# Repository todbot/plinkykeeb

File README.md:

# plinkykeeb

Simple MIDI controller using KB2040 and computer key switches, in Cherry MX or Kailh Choc versions

Also see: https://twitter.com/todbot/status/1492324272714366980__

And this demo video:

https://user-images.githubusercontent.com/274093/153778157-13a1d3d5-e82a-40dc-8635-7ddb3dfab898.mp4

Comparison in heights:

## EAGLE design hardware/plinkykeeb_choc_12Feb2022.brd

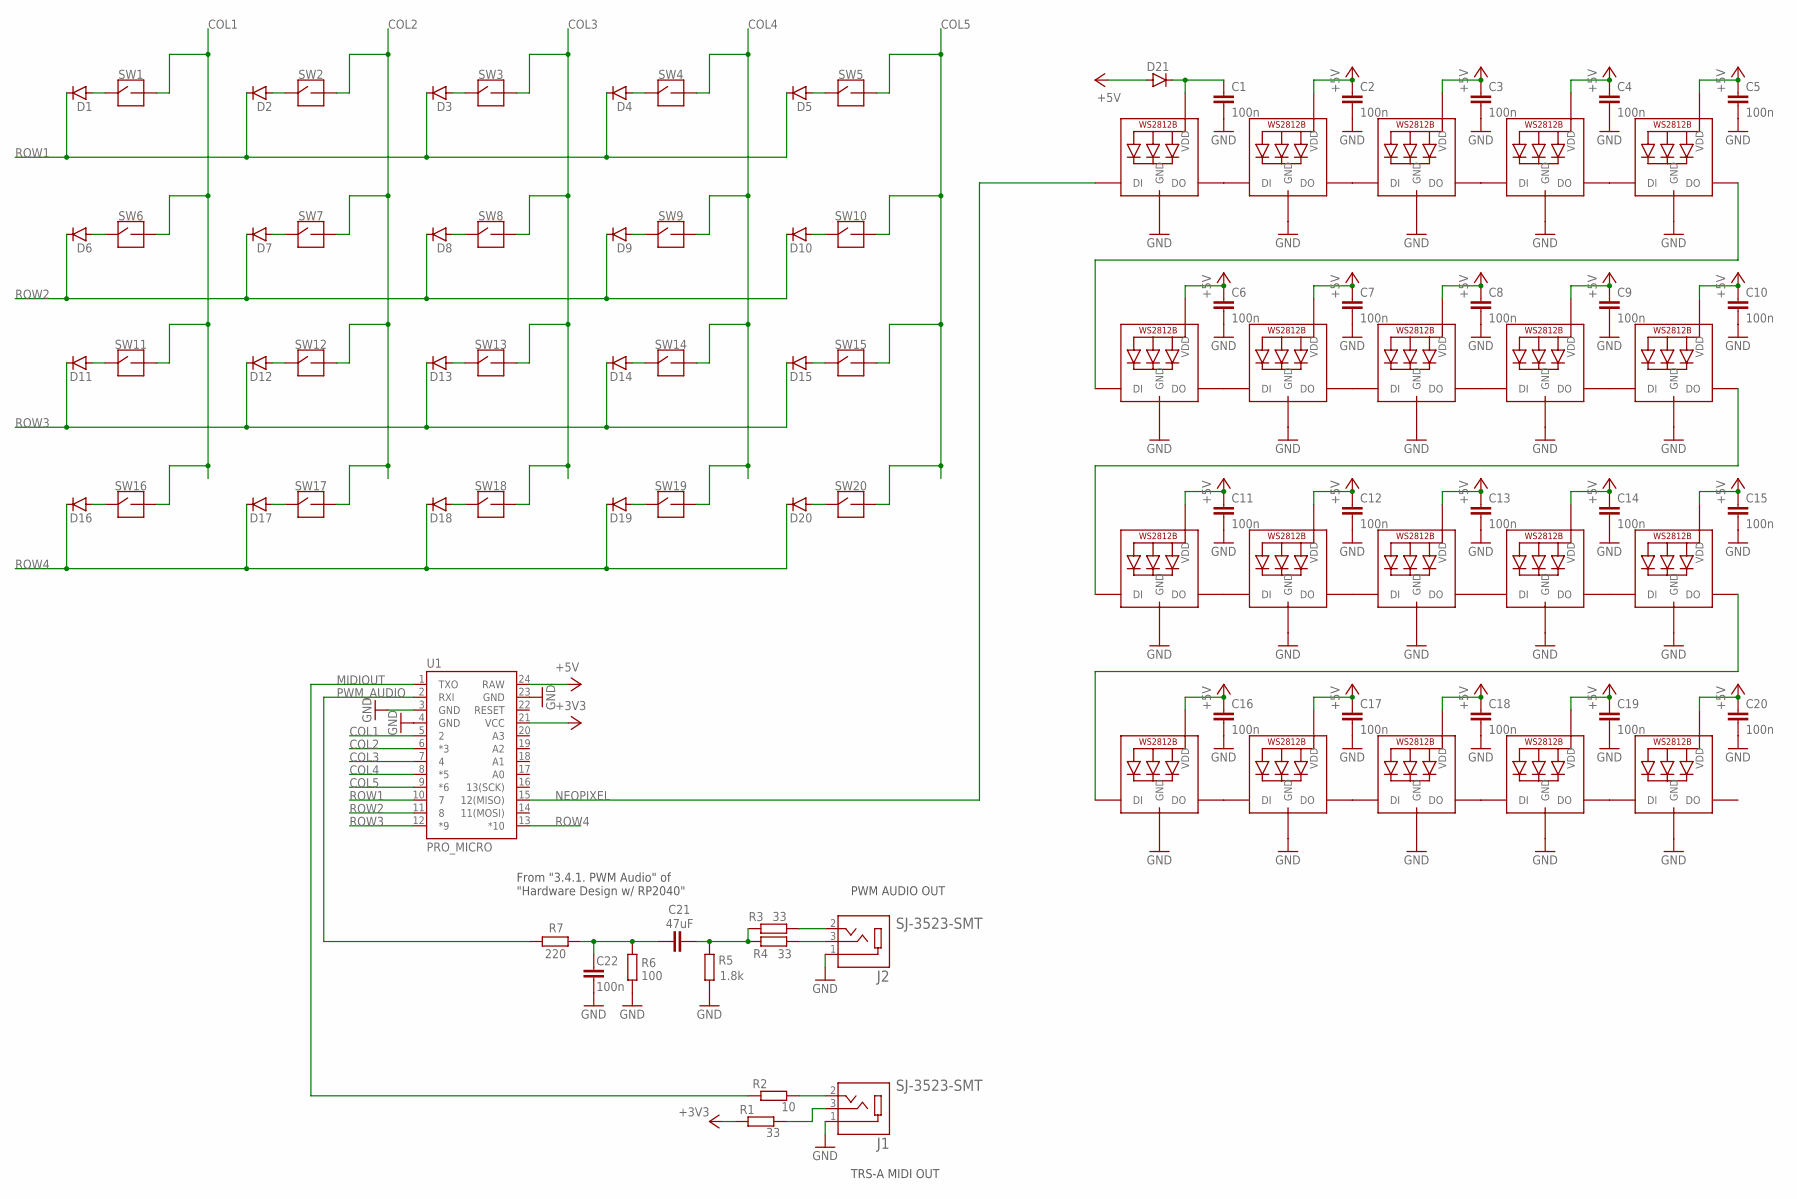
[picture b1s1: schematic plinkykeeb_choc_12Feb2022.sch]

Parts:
C1, C2, C3, C4, C5, C6, C7, C8, C9, C10, C11, C12, C13, C14, C15, C16, C17, C18, C19, C20, C22: 100n; C0805
C21: 47uF; C0805
D1, D2, D3, D4, D5, D6, D7, D8, D9, D10, D11, D12, D13, D14, D15, D16, D17, D18, D19, D20, D21: D-SOD123; SOD123
J1, J2: SJ-3523-SMT; CUI_SJ-3523-SMT
LED1, LED2, LED3, LED4, LED5, LED6, LED7, LED8, LED9, LED10, LED11, LED12, LED13, LED14, LED15, LED16, LED17, LED18, LED19, LED20: MICROBUILDER_WS2812B_SK6812E; MICROBUILDER_NEO3535_REVERSE
R1, R3, R4: 33; R0805
R2: 10; R0805
R5: 1.8k; R0805
R6: 100; R0805
R7: 220; R0805
SW1, SW2, SW3, SW4, SW5, SW6, SW7, SW8, SW9, SW10, SW11, SW12, SW13, SW14, SW15, SW16, SW17, SW18, SW19, SW20: KBD_SWITCHKALIH_CHOC_SOCKET; KALIH_SOCKET_CHOC
U1: PRO_MICRO; SPARKFUN_PRO_MICRO

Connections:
+3V3: R1.2, U1.21 (VCC)
+5V: C2.1, C3.1, C4.1, C5.1, C6.1, C7.1, C8.1, C9.1, C10.1, C11.1, C12.1, C13.1, C14.1, C15.1, C16.1, C17.1, C18.1, C19.1, C20.1, D21.2 (A), LED2.1-VDD (VDD), LED3.1-VDD (VDD), LED4.1-VDD (VDD), LED5.1-VDD (VDD), LED6.1-VDD (VDD), LED7.1-VDD (VDD), LED8.1-VDD (VDD), LED9.1-VDD (VDD), LED10.1-VDD (VDD), LED11.1-VDD (VDD), LED12.1-VDD (VDD), LED13.1-VDD (VDD), LED14.1-VDD (VDD), LED15.1-VDD (VDD), LED16.1-VDD (VDD), LED17.1-VDD (VDD), LED18.1-VDD (VDD), LED19.1-VDD (VDD), LED20.1-VDD (VDD), U1.24 (RAW)
COL1: SW1.2, SW6.2, SW11.2, SW16.2, U1.5 (2)
COL2: SW2.2, SW7.2, SW12.2, SW17.2, U1.6 (*3)
COL3: SW3.2, SW8.2, SW13.2, SW18.2, U1.7 (4)
COL4: SW4.2, SW9.2, SW14.2, SW19.2, U1.8 (*5)
COL5: SW5.2, SW10.2, SW15.2, SW20.2, U1.9 (*6)
GND: C1.2, C2.2, C3.2, C4.2, C5.2, C6.2, C7.2, C8.2, C9.2, C10.2, C11.2, C12.2, C13.2, C14.2, C15.2, C16.2, C17.2, C18.2, C19.2, C20.2, C22.2, J1.1, J2.1, LED1.3-GND (GND), LED2.3-GND (GND), LED3.3-GND (GND), LED4.3-GND (GND), LED5.3-GND (GND), LED6.3-GND (GND), LED7.3-GND (GND), LED8.3-GND (GND), LED9.3-GND (GND), LED10.3-GND (GND), LED11.3-GND (GND), LED12.3-GND (GND), LED13.3-GND (GND), LED14.3-GND (GND), LED15.3-GND (GND), LED16.3-GND (GND), LED17.3-GND (GND), LED18.3-GND (GND), LED19.3-GND (GND), LED20.3-GND (GND), R5.2, R6.1, U1.3 (GND), U1.4 (GND), U1.23 (GND)
MIDIOUT: R2.2, U1.1 (TXO)
unnamed: LED1.2-DOUT (DO), LED2.4-DIN (DI)
unnamed: LED2.2-DOUT (DO), LED3.4-DIN (DI)
unnamed: LED3.2-DOUT (DO), LED4.4-DIN (DI)
unnamed: LED4.2-DOUT (DO), LED5.4-DIN (DI)
unnamed: LED5.2-DOUT (DO), LED6.4-DIN (DI)
unnamed: D1.2 (A), SW1.1
unnamed: D2.2 (A), SW2.1
unnamed: D3.2 (A), SW3.1
unnamed: D4.2 (A), SW4.1
unnamed: D5.2 (A), SW5.1
unnamed: C1.1, D21.1 (C), LED1.1-VDD (VDD)
unnamed: D6.2 (A), SW6.1
unnamed: D18.2 (A), SW18.1
unnamed: D8.2 (A), SW8.1
unnamed: D9.2 (A), SW9.1
unnamed: D10.2 (A), SW10.1
unnamed: D11.2 (A), SW11.1
unnamed: D12.2 (A), SW12.1
unnamed: D13.2 (A), SW13.1
unnamed: D14.2 (A), SW14.1
unnamed: D15.2 (A), SW15.1
unnamed: D16.2 (A), SW16.1
unnamed: D17.2 (A), SW17.1
unnamed: D19.2 (A), SW19.1
unnamed: D20.2 (A), SW20.1
unnamed: LED7.2-DOUT (DO), LED8.4-DIN (DI)
unnamed: LED8.2-DOUT (DO), LED9.4-DIN (DI)
unnamed: LED9.2-DOUT (DO), LED10.4-DIN (DI)
unnamed: LED10.2-DOUT (DO), LED11.4-DIN (DI)
unnamed: LED11.2-DOUT (DO), LED12.4-DIN (DI)
unnamed: LED6.2-DOUT (DO), LED7.4-DIN (DI)
unnamed: D7.2 (A), SW7.1
unnamed: LED13.2-DOUT (DO), LED14.4-DIN (DI)
unnamed: LED14.2-DOUT (DO), LED15.4-DIN (DI)
unnamed: LED15.2-DOUT (DO), LED16.4-DIN (DI)
unnamed: LED16.2-DOUT (DO), LED17.4-DIN (DI)
unnamed: LED17.2-DOUT (DO), LED18.4-DIN (DI)
unnamed: LED12.2-DOUT (DO), LED13.4-DIN (DI)
unnamed: LED19.2-DOUT (DO), LED20.4-DIN (DI)
unnamed: LED18.2-DOUT (DO), LED19.4-DIN (DI)
unnamed: J1.2, R2.1
unnamed: J1.3, R1.1
unnamed: J2.2, R3.1
unnamed: J2.3, R4.1
unnamed: C21.2, R3.2, R4.2, R5.1
unnamed: C21.1, C22.1, R6.2, R7.1
NEOPIXEL: LED1.4-DIN (DI), U1.15 (12(MISO))
PWM_AUDIO: R7.2, U1.2 (RXI)
ROW1: D1.1 (C), D2.1 (C), D3.1 (C), D4.1 (C), D5.1 (C), U1.10 (7)
ROW2: D6.1 (C), D7.1 (C), D8.1 (C), D9.1 (C), D10.1 (C), U1.11 (8)
ROW3: D11.1 (C), D12.1 (C), D13.1 (C), D14.1 (C), D15.1 (C), U1.12 (*9)
ROW4: D16.1 (C), D17.1 (C), D18.1 (C), D19.1 (C), D20.1 (C), U1.13 (*10)

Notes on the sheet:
From "3.4.1. PWM Audio" of "Hardware Design w/ RP2040"
PWM AUDIO OUT
TRS-A MIDI OUT

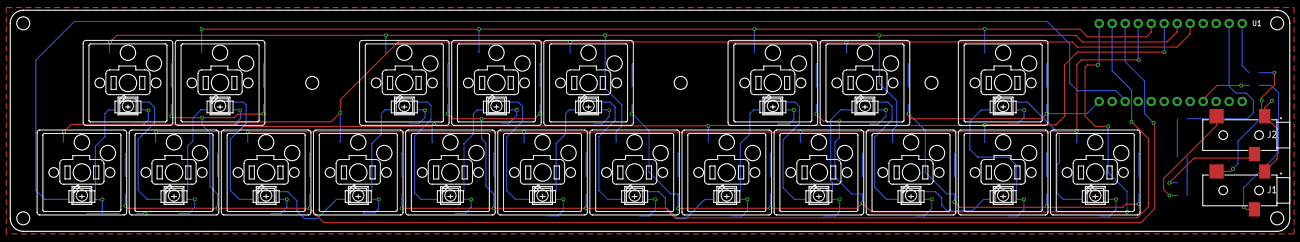
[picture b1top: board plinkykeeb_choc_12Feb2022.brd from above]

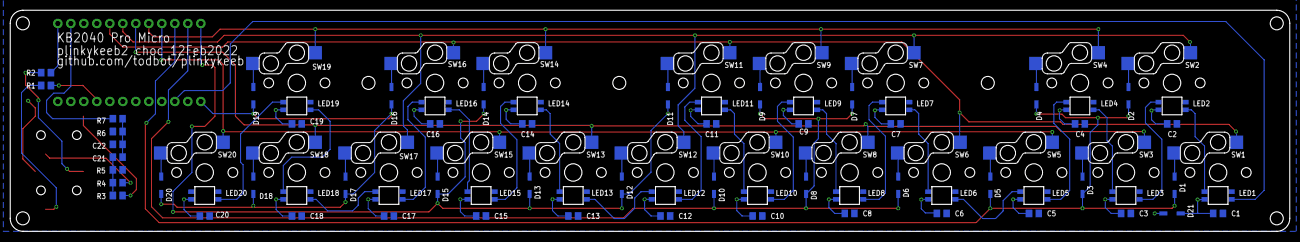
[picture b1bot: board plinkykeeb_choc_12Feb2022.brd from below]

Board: 2 copper layers, 249.9 x 43.1 mm, 93 parts (50 on the bottom side), 61 nets.

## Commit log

2022-01-24 first
2022-01-24 rejiggered audio out
2022-01-24 fix name
2022-01-25 shrink pcb a bit so parts can be 3dprinted
2022-01-26 submitted to pcbway
2022-02-05 docs
2022-02-08 finally put some code in github
2022-02-08 add wav files
2022-02-08 checked in arduino test
2022-02-08 arduino midi_test added
2022-02-10 clean up
2022-02-11 some cirpy updates
2022-02-12 new image
2022-02-12 updated case
2022-02-13 pontential choc version, a little smaller!
2022-02-13 added demo video
2022-02-14 some new sampleplayer thoughts
2022-02-15 circpy sampleplayer updates
2022-02-15 choc updates
2022-02-16 plinkykeeb_choc_12Feb sent to fab
2022-02-16 update midiout.py to keep LED on while key pressed
2022-02-24 mozzi test. mostly works. it is a synth!
2022-02-24 mozzi_test: LEDs go to core1 because they are naughty
2022-03-17 breakbeat mixer with syncd wavs
2025-01-03 small update to readme

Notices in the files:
parts and their libraries:
SparkFun-Boards: Licensing: Creative Commons ShareAlike 4.0 International - https://creativecommons.org/licenses/by-sa/4.0
